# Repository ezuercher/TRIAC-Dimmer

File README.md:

# TRIAC-Dimmer
Repository containing the design files for a TRIAC dimmer.

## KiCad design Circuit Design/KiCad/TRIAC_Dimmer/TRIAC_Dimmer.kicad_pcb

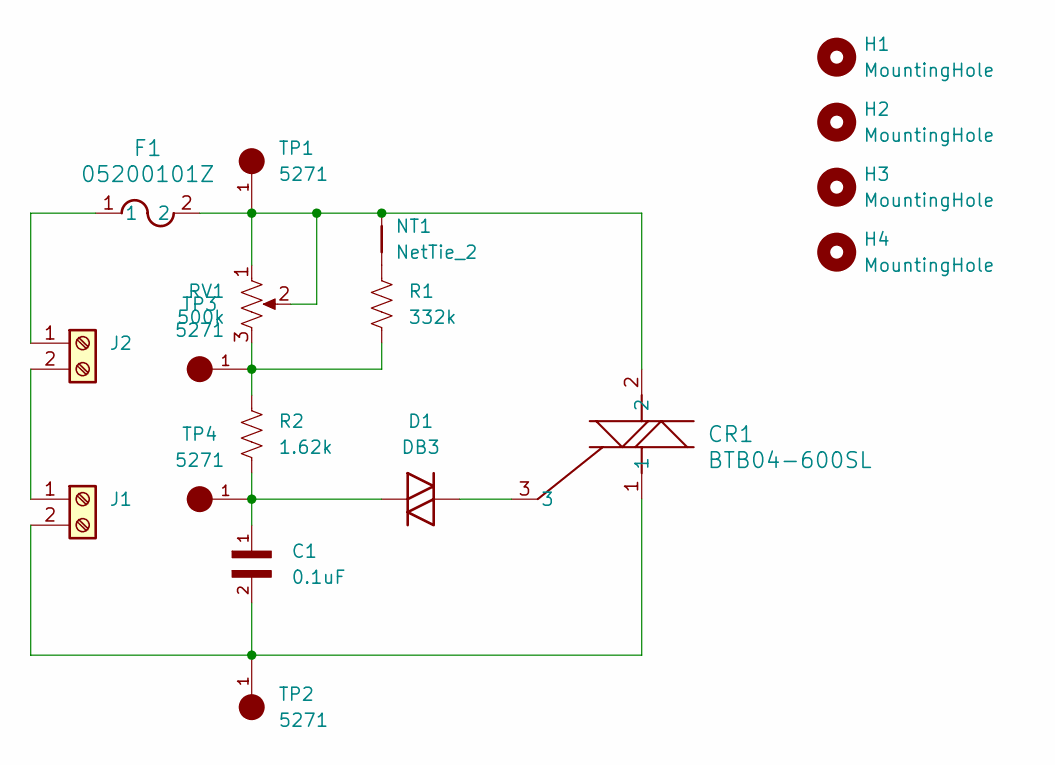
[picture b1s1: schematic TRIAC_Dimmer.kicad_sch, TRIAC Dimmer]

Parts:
C1: 0.1uF; CAPRR1500W80L1800T700H1250; PARTREV 2020-06
CR1: BTB04-600SL; TO-220AB_STM
D1: DB3; D_DO-35_SOD27_P7.62mm_Horizontal
F1: 05200101Z; FUSE_05200101Z_LTF
H1, H2, H3, H4: MountingHole; MountingHole_3.2mm_M3
J1, J2: Screw_Terminal_01x02; TerminalBlock_Phoenix_MKDS-1,5-2-5.08_1x02_P5.08mm_Horizont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
NT1: NetTie_2; NetTie-2_SMD_Pad0.5mm
R1: 332k; R_Axial_DIN0207_L6.3mm_D2.5mm_P7.62mm_Horizontal
R2: 1.62k; R_Axial_DIN0207_L6.3mm_D2.5mm_P7.62mm_Horizontal
RV1: 500k; Potentiometer_Bourns_PTV09A-2_Single_Horizontal
TP1, TP2, TP3, TP4: 5271; KEYSTONE_5271

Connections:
unnamed: CR1.2, F1.2, NT1.2, RV1.1, RV1.2, TP1.1
unnamed: CR1.3, D1.2 (A)
unnamed: C1.1, D1.1 (K), R2.2, TP4.1
unnamed: J1.1, J2.2
unnamed: C1.2, CR1.1, J1.2, TP2.1
unnamed: F1.1, J2.1
unnamed: NT1.1, R1.1
unnamed: R1.2, R2.1, RV1.3, TP3.1

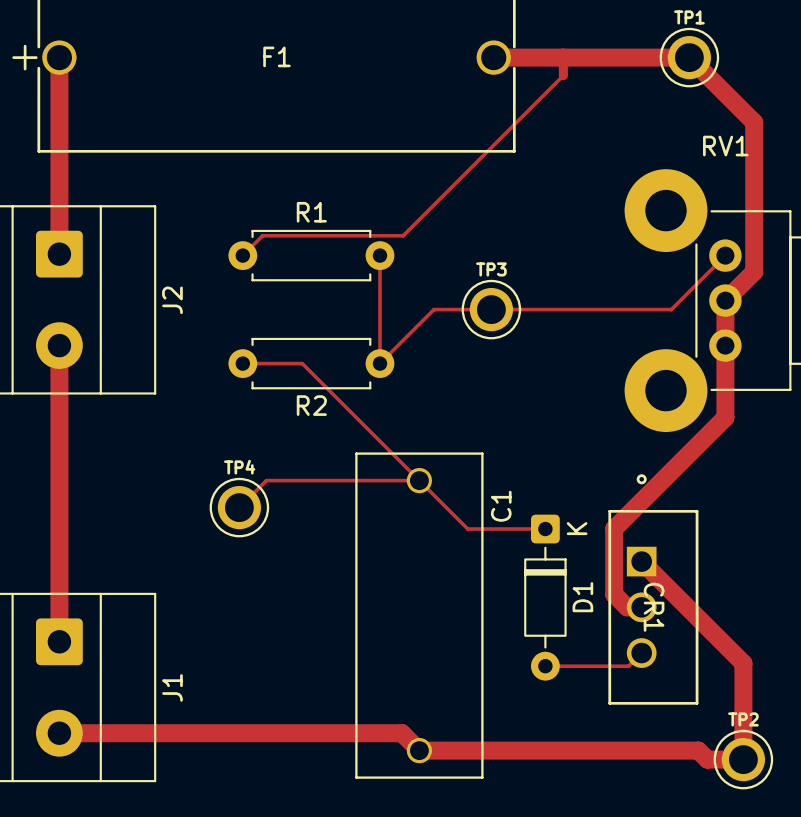
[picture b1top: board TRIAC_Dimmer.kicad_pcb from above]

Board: 2 copper layers, 18 parts (0 on the bottom side), 8 nets.

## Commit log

2025-08-20 Cleaned up repository
2025-08-20 Finished analytical portion of report
2025-08-20 Working on documenting simulation results
2025-08-22 Filling out simulation section of report
2025-08-22 Finished simulation portion of report
2025-08-25 PCB libraries were global, made them local
2025-08-25 Was going to build cable, now going with screw terminals
2025-08-29 Rough layout complete
